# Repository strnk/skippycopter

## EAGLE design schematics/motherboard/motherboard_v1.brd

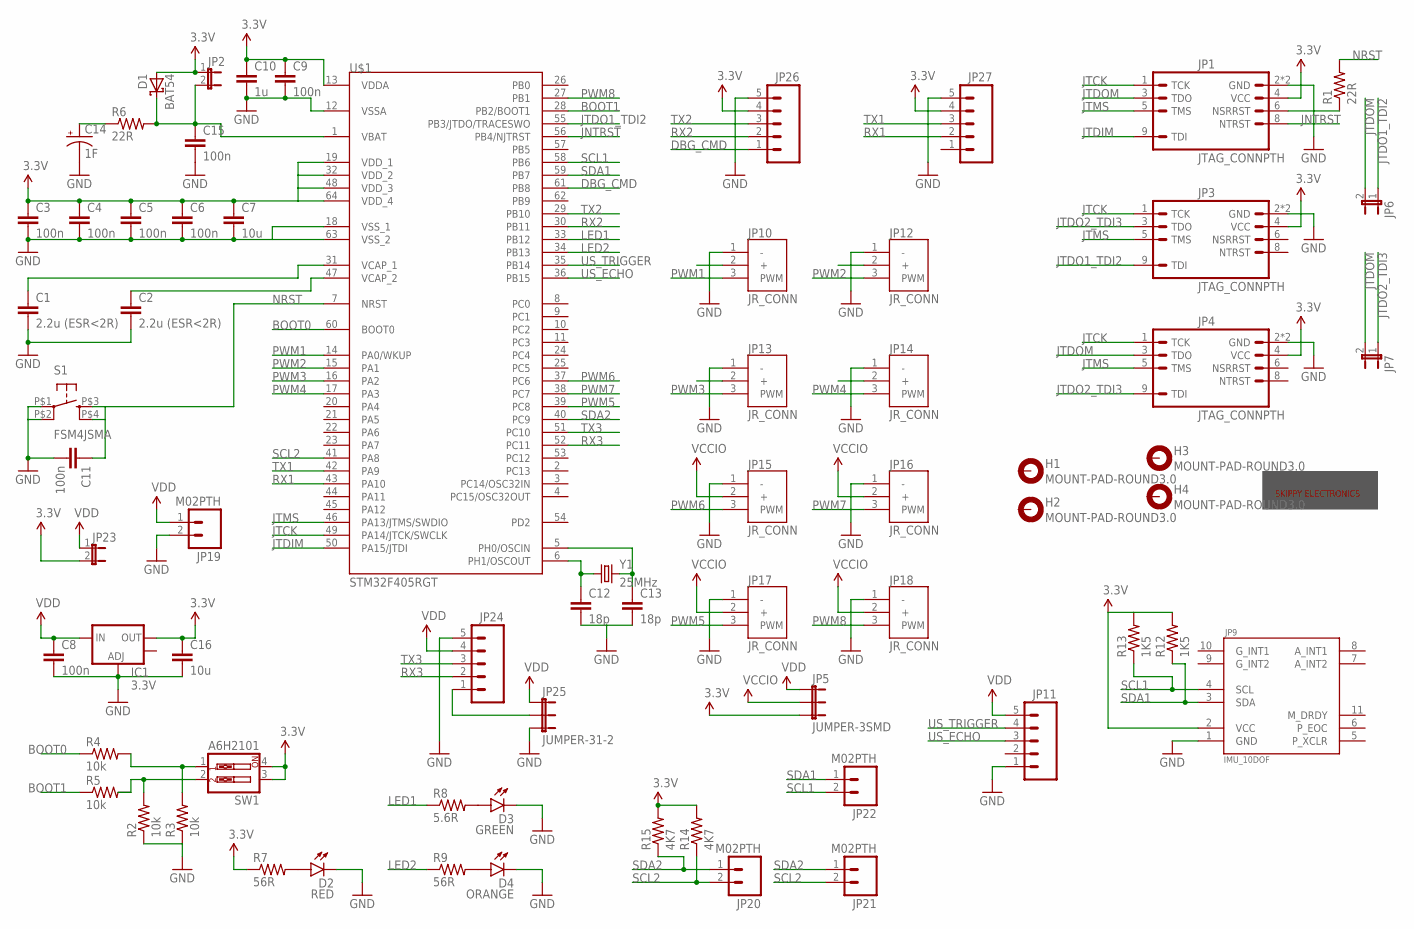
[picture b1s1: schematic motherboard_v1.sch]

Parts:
C1, C2: 2.2u (ESR<2R); 1206
C3, C4, C5, C6, C9, C15: 100n; 0805
C7, C16: 10u; 1206
C8, C11: 100n; 1206
C10: 1u; 1206
C12, C13: 18p; 1206
C14: 1F; CPOL-RADIAL-D165-P508
D1: BAT54; SOT23
D2: RED; LED-1206
D3: GREEN; LED-1206
D4: ORANGE; LED-1206
H1, H2, H3, H4: MOUNT-PAD-ROUND3.0; 3,0-PAD
IC1: 3.3V; SOT223
JP1, JP3, JP4: JTAG_CONNPTH; AVR_ICSP
JP2, JP6, JP7, JP23: JUMPER-2SMD-NO; SJ_2S-NO
JP5: JUMPER-3SMD; SJ_3
JP9: IMU_10DOF
JP10, JP12, JP13, JP14, JP15, JP16, JP17, JP18: JR_CONN; 1X03
JP11, JP24, JP26, JP27: M05PTH; 1X05
JP19, JP20, JP21, JP22: M02PTH; 1X02
JP25: JUMPER-31-2; SJ_3_PASTE1&2
R1, R6: 22R; 1206
R2, R3, R4, R5: 10k; 1206
R7, R9: 56R; 1206
R8: 5.6R; 1206
R12, R13: 1K5; 1206
R14, R15: 4K7; 1206
S1: FSM4JSMA; TYCO-FSM4JSMA
SW1: A6H2101; DIPSWITCH-02-50MIL
U$1: STM32F405RGT; LQFP-ST-64-2
U$2: SKIPPYTXT-PLC-10MM
Y1: 25MHz; HC49UP

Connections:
3.3V: C3.1, C4.1, C5.1, C6.1, C7.1, C9.1, C10.1, C16.1, D1.1 (A), IC1.2 (OUT), JP1.4 (VCC), JP2.1, JP3.4 (VCC), JP4.4 (VCC), JP5.3, JP9.2 (VCC), JP23.2, JP26.4, JP27.4, R7.1, R12.2, R13.2, R14.2, R15.2, SW1.3, SW1.4, U$1.13 (VDDA), U$1.19 (VDD_1), U$1.32 (VDD_2), U$1.48 (VDD_3), U$1.64 (VDD_4)
BOOT0: R4.1, U$1.60 (BOOT0)
BOOT1: R5.1, U$1.28 (PB2/BOOT1)
DBG_CMD: JP26.1, U$1.61 (PB8)
GND: C1.2, C2.2, C3.2, C4.2, C5.2, C6.2, C7.2, C8.2, C9.2, C10.2, C11.2, C12.2, C13.2, C14.2 (-), C15.2, C16.2, D2.C, D3.C, D4.C, IC1.1 (ADJ), JP1.2 (GND), JP1.10 (GND), JP3.2 (GND), JP3.10 (GND), JP4.2 (GND), JP4.10 (GND), JP9.1 (GND), JP10.1 (-), JP11.1, JP12.1 (-), JP13.1 (-), JP14.1 (-), JP15.1 (-), JP16.1 (-), JP17.1 (-), JP18.1 (-), JP19.2, JP24.5, JP25.3, JP26.5, JP27.5, R2.1, R3.1, S1.P$1 (1), S1.P$2 (2), U$1.12 (VSSA), U$1.18 (VSS_1), U$1.63 (VSS_2)
JNTRST: JP1.8 (NTRST), U$1.56 (PB4/NJTRST)
JTCK: JP1.1 (TCK), JP3.1 (TCK), JP4.1 (TCK), U$1.49 (PA14/JTCK/SWCLK)
JTDIM: JP1.9 (TDI), U$1.50 (PA15/JTDI)
JTDO1_TDI2: JP3.9 (TDI), JP6.1, U$1.55 (PB3/JTDO/TRACESWO)
JTDO2_TDI3: JP3.3 (TDO), JP4.9 (TDI), JP7.1
JTDOM: JP1.3 (TDO), JP4.3 (TDO), JP6.2, JP7.2
JTMS: JP1.5 (TMS), JP3.5 (TMS), JP4.5 (TMS), U$1.46 (PA13/JTMS/SWDIO)
LED1: R8.1, U$1.33 (PB12)
LED2: R9.1, U$1.34 (PB13)
unnamed: C1.1, U$1.31 (VCAP_1)
unnamed: C2.1, U$1.47 (VCAP_2)
unnamed: C12.1, U$1.6 (PH1/OSCOUT), Y1.1
unnamed: JP1.6 (NSRRST), R1.1
unnamed: C13.1, U$1.5 (PH0/OSCIN), Y1.2
unnamed: R3.2, R4.2, SW1.1
unnamed: R2.2, R5.2, SW1.2
unnamed: D2.A, R7.2
unnamed: C14.1 (+), R6.1
unnamed: C15.1, D1.3 (C), JP2.2, R6.2, U$1.1 (VBAT)
unnamed: D3.A, R8.2
unnamed: JP24.1, JP25.2
unnamed: D4.A, R9.2
NRST: C11.1, R1.2, S1.P$3 (3), S1.P$4 (4), U$1.7 (NRST)
PWM1: JP10.3 (PWM), U$1.14 (PA0/WKUP)
PWM2: JP12.3 (PWM), U$1.15 (PA1)
PWM3: JP13.3 (PWM), U$1.16 (PA2)
PWM4: JP14.3 (PWM), U$1.17 (PA3)
PWM5: JP17.3 (PWM), U$1.39 (PC8)
PWM6: JP15.3 (PWM), U$1.37 (PC6)
PWM7: JP16.3 (PWM), U$1.38 (PC7)
PWM8: JP18.3 (PWM), U$1.27 (PB1)
RX1: JP27.2, U$1.43 (PA10)
RX2: JP26.2, U$1.30 (PB11)
RX3: JP24.2, U$1.52 (PC11)
SCL1: JP9.4 (SCL), JP22.2, R13.1, U$1.58 (PB6)
SCL2: JP20.2, JP21.2, R14.1, U$1.41 (PA8)
SDA1: JP9.3 (SDA), JP22.1, R12.1, U$1.59 (PB7)
SDA2: JP20.1, JP21.1, R15.1, U$1.40 (PC9)
TX1: JP27.3, U$1.42 (PA9)
TX2: JP26.3, U$1.29 (PB10)
TX3: JP24.3, U$1.51 (PC10)
US_ECHO: JP11.3, U$1.36 (PB15)
US_TRIGGER: JP11.4, U$1.35 (PB14)
VCCIO: JP5.2, JP15.2 (+), JP16.2 (+), JP17.2 (+), JP18.2 (+)
VDD: C8.1, IC1.3 (IN), JP5.1, JP11.5, JP19.1, JP23.1, JP24.4, JP25.1

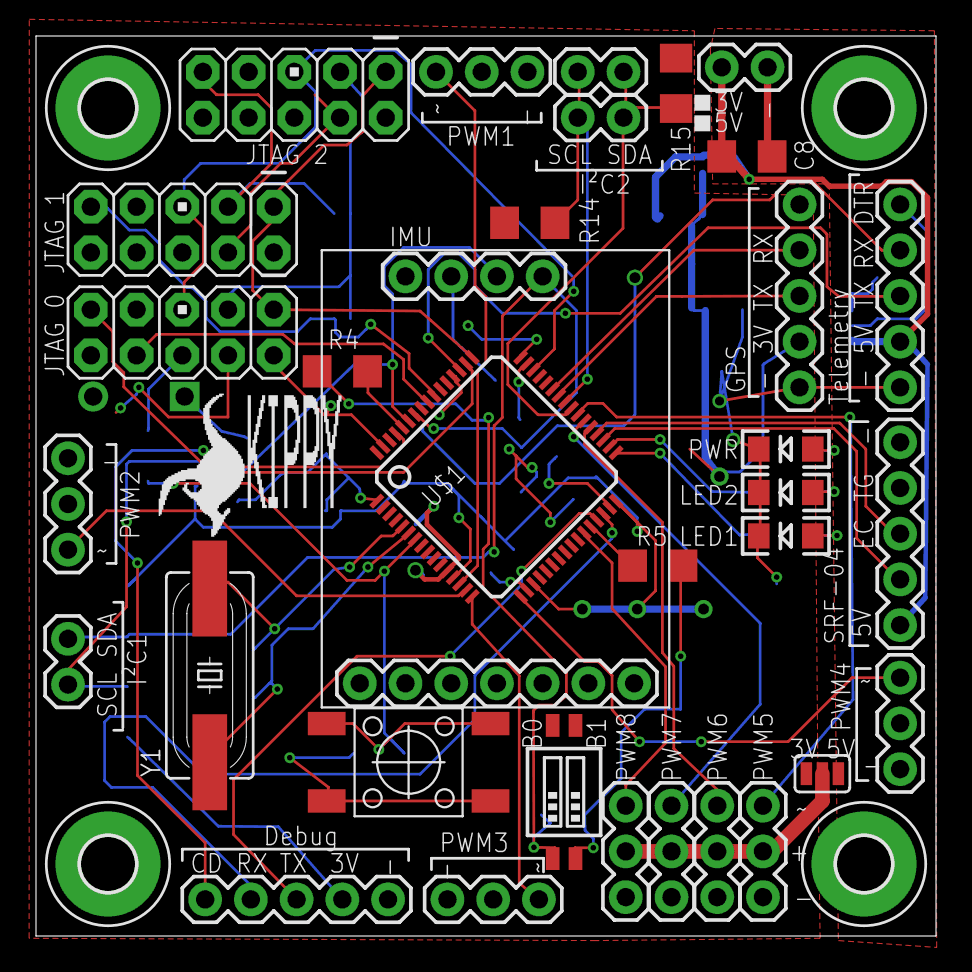
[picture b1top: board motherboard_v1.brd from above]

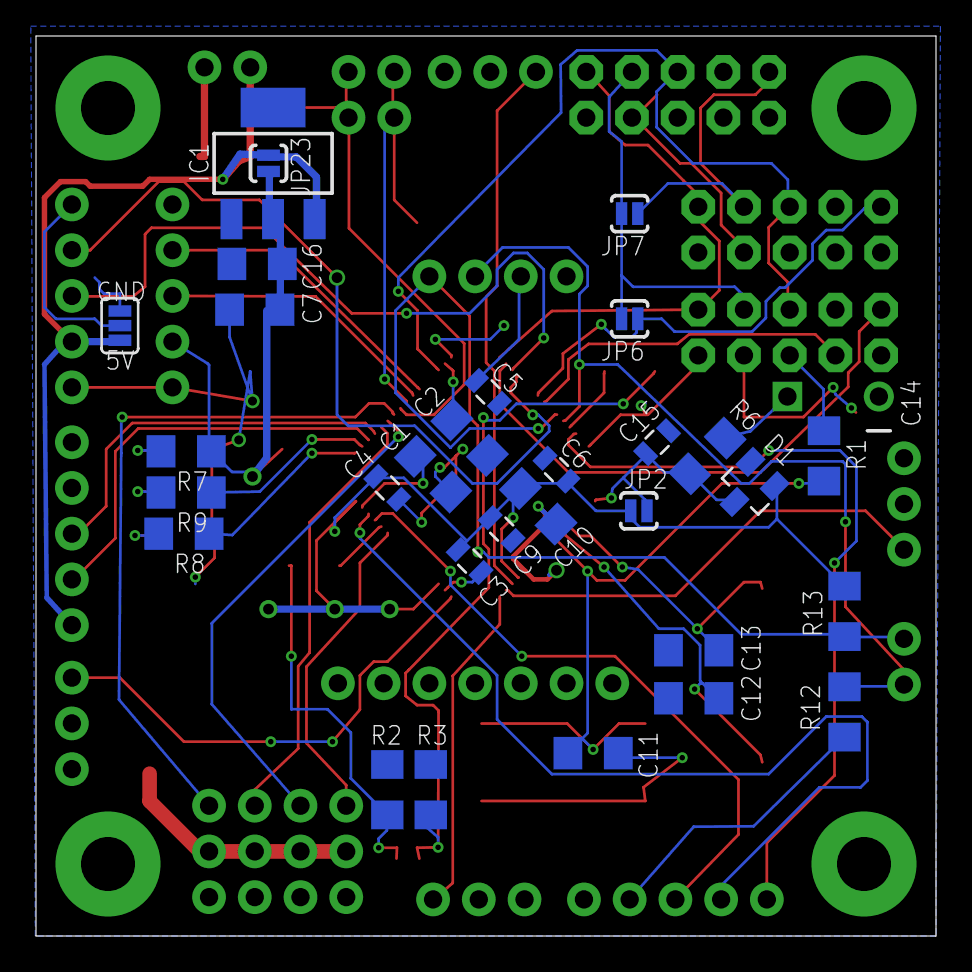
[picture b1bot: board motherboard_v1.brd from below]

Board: 2 copper layers, 50.0 x 50.0 mm, 69 parts (31 on the bottom side), 50 nets.

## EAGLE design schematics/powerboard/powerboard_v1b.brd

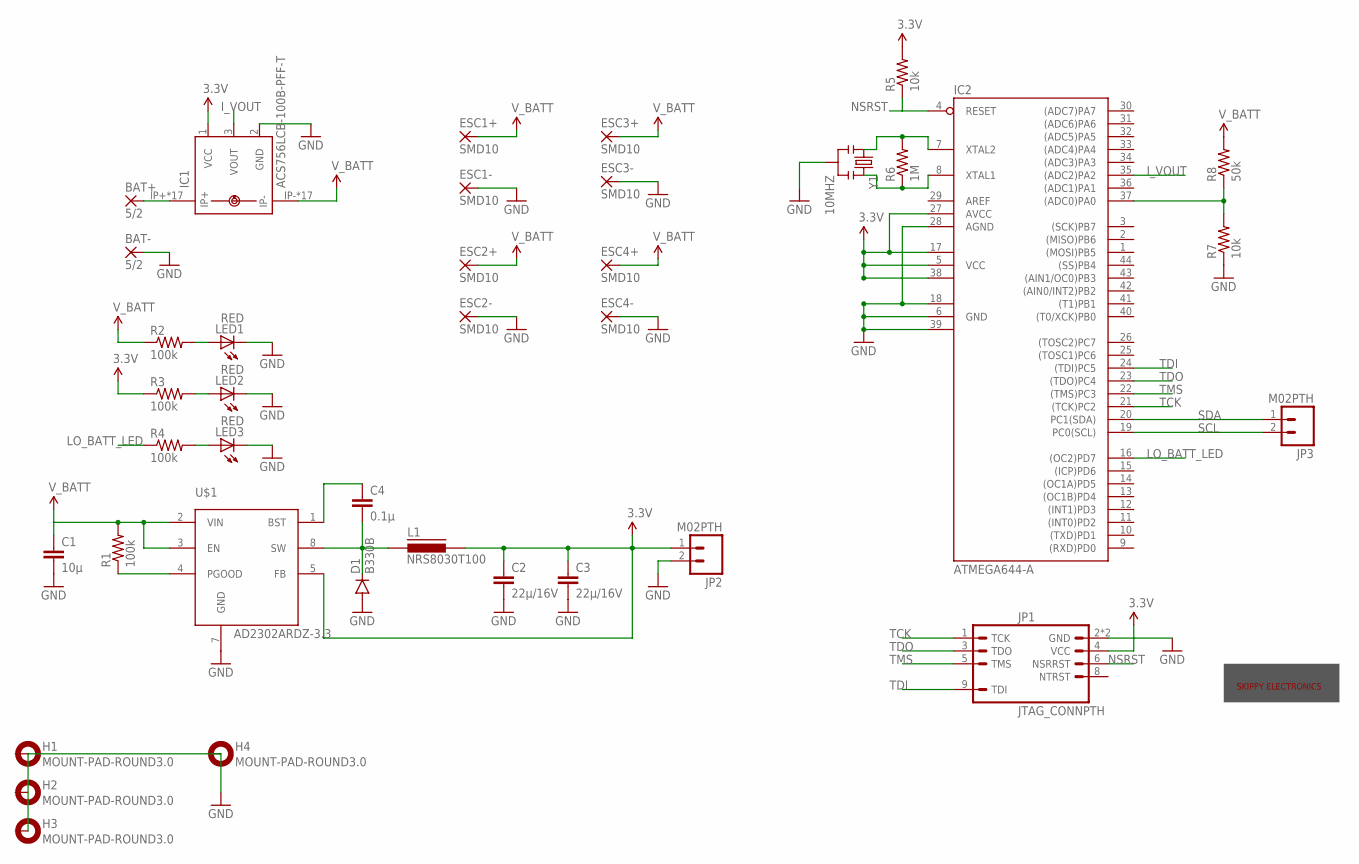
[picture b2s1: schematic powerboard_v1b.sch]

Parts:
BAT+: 5/2
BAT-: 5/2
C1: 10µ; 1206
C2, C3: 22µ/16V; 1206
C4: 0.1µ; 1206
D1: B330B; SMB-DIODE
ESC1+, ESC1-, ESC2+, ESC2-, ESC3+, ESC3-, ESC4+, ESC4-: SMD10; SMD5.08-10.16
H1, H2, H3, H4: MOUNT-PAD-ROUND3.0; 3,0-PAD
IC1: ACS756LCB-100B-PFF-T; CB-PFF
IC2: ATMEGA644-A; TQFP44
JP1: JTAG_CONNPTH; AVR_ICSP
JP2, JP3: M02PTH; 1X02
L1: NRS8030T100; NRS8030
LED1, LED2, LED3: RED; LED_1206
R1, R2, R3, R4: 100k; 1206
R5, R7: 10k; 1206
R6: 1M; 1206
R8: 50k; 1206
U$1: AD2302ARDZ-3.3; SO8
U$2: SKIPPYTXT-PLC-10MM
Y1: 10MHZ; RESONATOR-SMD

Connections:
3.3V: C2.1, C3.1, IC1.1 (VCC), IC2.5 (VCC), IC2.17 (VCC1), IC2.27 (AVCC), IC2.38 (VCC2), JP1.4 (VCC), JP2.1, L1.P$2 (2), R3.1, R5.2, U$1.5 (FB)
GND: BAT-.P$1, C1.2, C2.2, C3.2, D1.A, ESC1-.P$1, ESC1-.P$2, ESC2-.P$1, ESC2-.P$2, ESC3-.P$1, ESC3-.P$2, ESC4-.P$1, ESC4-.P$2, IC1.2 (GND), IC2.6 (GND), IC2.18 (GND1), IC2.28 (AGND), IC2.39 (GND2), JP1.2 (GND), JP1.10 (GND), JP2.2, LED1.C, LED2.C, LED3.C, R7.1, U$1.7 (GND), Y1.2
I_VOUT: IC1.3 (VOUT), IC2.35 ((ADC2)PA2)
LO_BATT_LED: IC2.16 ((OC2)PD7), R4.1
unnamed: BAT+.P$1, IC1.IP+, IC1.IP+@2 (IP+), IC1.IP+@3 (IP+), IC1.IP+@4 (IP+), IC1.IP+@5 (IP+), IC1.IP+@6 (IP+), IC1.IP+@7 (IP+), IC1.IP+@8 (IP+), IC1.IP+@9 (IP+), IC1.IP+@10 (IP+), IC1.IP+@11 (IP+), IC1.IP+@12 (IP+), IC1.IP+@13 (IP+), IC1.IP+@14 (IP+), IC1.IP+@15 (IP+), IC1.IP+@16 (IP+), IC1.IP+@17 (IP+)
unnamed: C4.2, D1.C, L1.P$1 (1), U$1.8 (SW)
unnamed: R1.1, U$1.4 (PGOOD)
unnamed: LED1.A, R2.2
unnamed: C4.1, U$1.1 (BST)
unnamed: LED2.A, R3.2
unnamed: LED3.A, R4.2
unnamed: IC2.7 (XTAL2), R6.2, Y1.1
unnamed: IC2.8 (XTAL1), R6.1, Y1.3
unnamed: IC2.37 ((ADC0)PA0), R7.2, R8.1
NSRST: IC2.4 (RESET), JP1.6 (NSRRST), R5.1
SCL: IC2.19 (PC0(SCL)), JP3.2
SDA: IC2.20 (PC1(SDA)), JP3.1
TCK: IC2.21 ((TCK)PC2), JP1.1 (TCK)
TDI: IC2.24 ((TDI)PC5), JP1.9 (TDI)
TDO: IC2.23 ((TDO)PC4), JP1.3 (TDO)
TMS: IC2.22 ((TMS)PC3), JP1.5 (TMS)
V_BATT: C1.1, ESC1+.P$1, ESC1+.P$2, ESC2+.P$1, ESC2+.P$2, ESC3+.P$1, ESC3+.P$2, ESC4+.P$1, ESC4+.P$2, IC1.IP-, IC1.IP-@2 (IP-), IC1.IP-@3 (IP-), IC1.IP-@4 (IP-), IC1.IP-@5 (IP-), IC1.IP-@6 (IP-), IC1.IP-@7 (IP-), IC1.IP-@8 (IP-), IC1.IP-@9 (IP-), IC1.IP-@10 (IP-), IC1.IP-@11 (IP-), IC1.IP-@12 (IP-), IC1.IP-@13 (IP-), IC1.IP-@14 (IP-), IC1.IP-@15 (IP-), IC1.IP-@16 (IP-), IC1.IP-@17 (IP-), R1.2, R2.1, R8.2, U$1.2 (VIN), U$1.3 (EN)

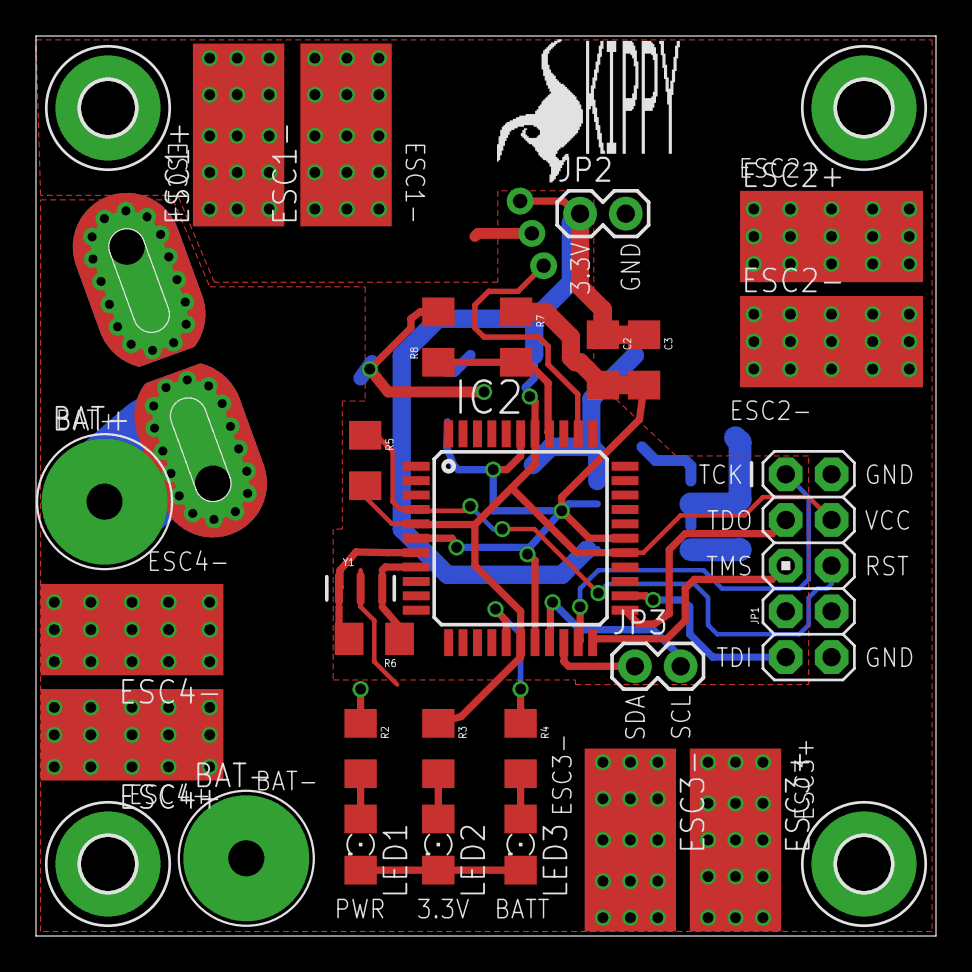
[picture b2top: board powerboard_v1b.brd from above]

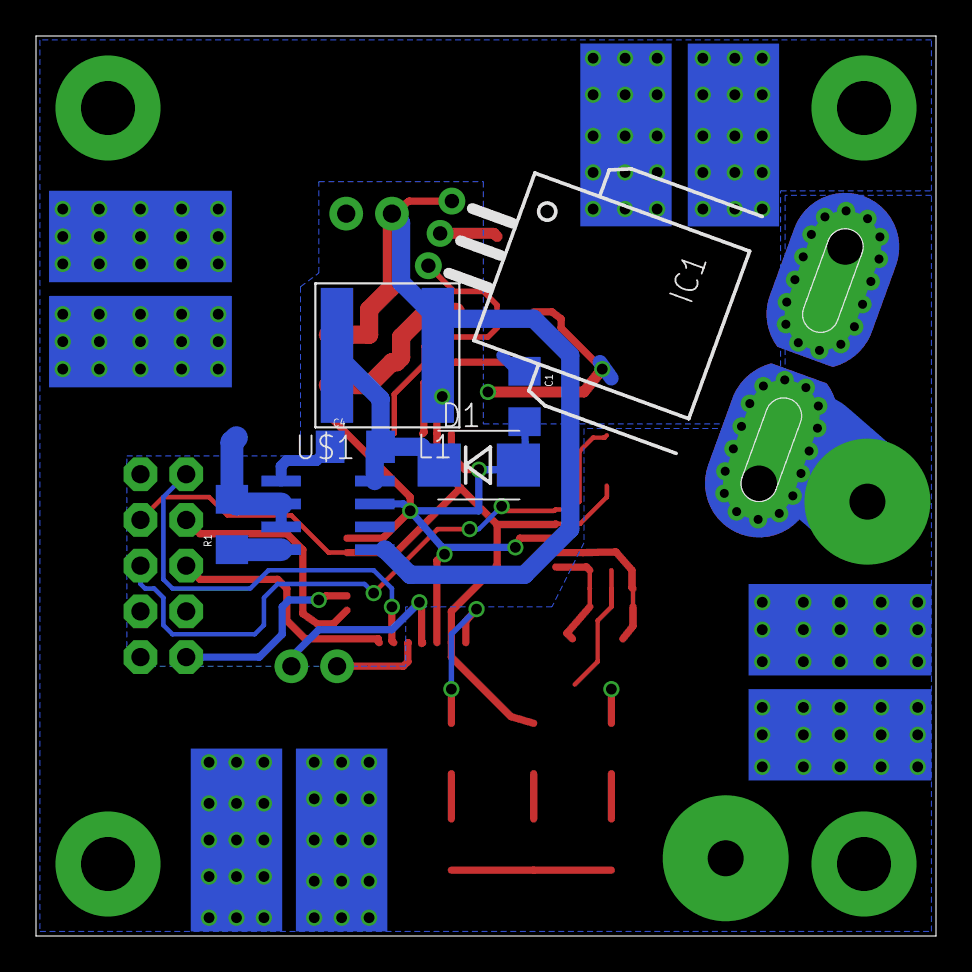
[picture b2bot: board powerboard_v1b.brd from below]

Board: 2 copper layers, 50.0 x 50.0 mm, 39 parts (7 on the bottom side), 22 nets.

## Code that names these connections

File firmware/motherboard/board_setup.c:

#include <libopencm3/stm32/rcc.h>
#include <libopencm3/stm32/gpio.h>
#include "board_setup.h"
#include "config.h"

/* Set STM32 to 168 MHz. */
void clock_setup(void)
{
    rcc_clock_setup_hse_3v3(&hse_25mhz_3v3[CLOCK_3V3_168MHZ]);
}

void gpio_setup(void)
{
    // Enable GPIO clocks
    rcc_periph_clock_enable(RCC_GPIOA);
    rcc_periph_clock_enable(RCC_GPIOB);
    rcc_periph_clock_enable(RCC_GPIOC);
			 
    /* PA0/1/2/3 as TIM2 CH1/2/3/4 */
    gpio_mode_setup(GPIOA, GPIO_MODE_AF, GPIO_PUPD_NONE, GPIO0 | GPIO1 | GPIO2 | GPIO3);
    gpio_set_output_options(GPIOA, GPIO_OTYPE_PP, GPIO_OSPEED_50MHZ, GPIO0 | GPIO1 | GPIO2 | GPIO3);
    gpio_set_af(GPIOA, GPIO_AF1, GPIO0 | GPIO1 | GPIO2 | GPIO3);

    /* PA8 as I2C3 SCL */
    gpio_mode_setup(GPIOA, GPIO_MODE_AF, GPIO_PUPD_NONE, GPIO8);
    gpio_set_output_options(GPIOA, GPIO_OTYPE_OD, GPIO_OSPEED_50MHZ, GPIO8);
    gpio_set_af(GPIOA, GPIO_AF4, GPIO8);

    /* PA9/10 as USART1 TX/RX */
    gpio_mode_setup(GPIOA, GPIO_MODE_AF, GPIO_PUPD_NONE, GPIO9 | GPIO10);
    gpio_set_af(GPIOA, GPIO_AF7, GPIO9 | GPIO10);

    /* PB1 as TIM3 CH4 */
    gpio_mode_setup(GPIOB, GPIO_MODE_AF, GPIO_PUPD_NONE, GPIO1);
    gpio_set_af(GPIOB, GPIO_AF2, GPIO1);

    /* PB6/7 as I2C1 SCL/SDA */
    gpio_mode_setup(GPIOB, GPIO_MODE_AF, GPIO_PUPD_NONE, GPIO6 | GPIO7);
    gpio_set_output_options(GPIOB, GPIO_OTYPE_OD, GPIO_OSPEED_50MHZ, GPIO6 | GPIO7);
    gpio_set_af(GPIOB, GPIO_AF4, GPIO6 | GPIO7);

	/* PB10/11 as USART3 TX/RX */
	gpio_mode_setup(GPIOB, GPIO_MODE_AF, GPIO_PUPD_NONE, GPIO10 | GPIO11);
	gpio_set_af(GPIOB, GPIO_AF7, GPIO10 | GPIO11);

    /* PB12/13 as LED1/LED2 */
    gpio_mode_setup(GPIOB, GPIO_MODE_OUTPUT, GPIO_PUPD_NONE, GPIO12 | GPIO13);

    /* PB14/15 as US_TRIGGER/US_ECHO */
    gpio_mode_setup(GPIOB, GPIO_MODE_OUTPUT, GPIO_PUPD_NONE, GPIO14);
    gpio_mode_setup(GPIOB, GPIO_MODE_INPUT, GPIO_PUPD_NONE, GPIO15);

    /* PC6/7 as TIM3 CH1/2 */
    gpio_mode_setup(GPIOC, GPIO_MODE_AF, GPIO_PUPD_NONE, GPIO6 | GPIO7 | GPIO8);
    gpio_set_af(GPIOC, GPIO_AF2, GPIO6 | GPIO7);

    #ifdef USE_PPM_INPUT
    /* PC8 as TIM8 CH3 */
    gpio_set_af(GPIOC, GPIO_AF3, GPIO8);
    #else
    /* PC8 as TIM3 CH3 */
    gpio_set_af(GPIOC, GPIO_AF2, GPIO8);
    #endif

    /* PC9 as I2C3 SDA */
    gpio_mode_setup(GPIOC, GPIO_MODE_AF, GPIO_PUPD_NONE, GPIO9);
    gpio_set_output_options(GPIOC, GPIO_OTYPE_OD, GPIO_OSPEED_50MHZ, GPIO9);
    gpio_set_af(GPIOC, GPIO_AF4, GPIO9);

    /* PC10/11 as UART4 TX/RX */
    gpio_mode_setup(GPIOC, GPIO_MODE_AF, GPIO_PUPD_NONE, GPIO10 | GPIO11);
    gpio_set_af(GPIOC, GPIO_AF8, GPIO10 | GPIO11);

    // Enable timers clocks
    rcc_periph_clock_enable(RCC_PWM_LO_TIMER);
    rcc_periph_clock_enable(RCC_PWM_HI_TIMER);
    rcc_periph_clock_enable(RCC_PPM_TIMER);

    // Enable UARTs clocks
    rcc_periph_clock_enable(RCC_UART_DEBUG);
    rcc_periph_clock_enable(RCC_UART_GPS);
}

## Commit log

2013-12-06 Directory structure
2013-12-06 Battery docs
2013-12-06 ESC docs
2013-12-06 IMU docs
2013-12-06 Motherboard docs
2013-12-06 Miscellaneous docs
2013-12-21 SeeedStudio libraries and motherboard schematic draft
2013-12-21 New STM32F405RGT symbol in stm32 lib
2013-12-24 Quadricopter sizing excel sheet
2014-01-06 Skippy logos
2014-01-06 Bitmap (300dpi) versions of the logos
2014-01-06 Eagle library of Skippy logos
2014-01-07 Adding documentation for dual USB UART/FIFO FT2232
2015-02-06 ACS756 datasheet + eagle libs
2015-02-07 Eagle lib update & logos
2015-02-08 Added Sparkfun Eagle libs
2015-02-08 Moved Sparkfun lib to 3rd-party
2015-02-08 Changed README to markdown format
2015-02-08 Reorganized libs, added DC/DC buck converter and power board
2015-02-08 Inductor lib and powerboard 5V rail
2015-02-09 Power board finalized
2015-02-09 Power board PCB placement
2015-02-11 New PCB for power board
2015-02-19 Lower resolution logo for Gerber export
2015-02-19 Powerboard PCB and schematics revisions a and b
2015-02-19 Low-resolution logo
2015-02-19 Seeedstudio DRU and CAM update
2015-02-19 Powerboard PCB rev 1b RTM Gerber export for Seeedstudio
2015-02-20 Seeedstudio Powerboard RTM rev 1b fix
2015-05-01 Motherboard schematic draft
2015-05-03 Motherboard reference design
2015-05-04 Library refactor and motherboard update
2015-05-04 Bluetooth debug module and external boards lib. Motherboard update
2015-05-05 Motherboard update and PCB draft
2015-05-06 MB PCB update
2015-05-07 Motherboard update with almost-ready routing
2015-05-08 Motherboard v1 RTM
2015-05-10 Dependencies help file
2015-05-10 Powerboard test firmware
2015-05-10 OpenOCD scripts and global Makefile
2015-05-11 Motherboard printouts and boards documentation
2015-05-17 Chain test with STM32 discovery
2015-05-26 Software dependencies and Monitor UI draft
2015-05-26 Rework of the openOCD scripts to support single card flashing and MB UART test with console support
2015-05-27 Directory typo fix
2015-05-28 Fixes issues #1 and #2
2015-05-28 Motherboard IMU test
2015-05-29 Removed old powerboard revs
2015-05-29 Add the RTM dir to vendored folder in gitattributes
2015-05-29 SkippyMonitor GI/CLI application draft
2015-05-30 Build instruction update for Linux
2015-05-30 Attributes update
2015-05-30 IMU compass example
2015-05-31 Motherboard firmware C++ rework
2015-05-31 I2C write fix and ADXL345 test
2015-05-31 Full IMU draft + temporal scheduler
2015-06-03 Skippy Monitor update with IMU plotting support
2015-06-03 Gyro register reading fix and 115200baud UART. IMU debug
2015-06-03 Documentation update
2015-06-08 L3G4200D reading problem fix
2015-06-08 Madgwick2011 fusion algorithm test with live 3D visualization
2015-07-05 PWM peripheral + ESC arm
2015-07-05 Performance counters
2015-07-05 Small fix. in the Sys. Scheduler debug log
2015-07-06 CLI interface draft. CLI PWM support
2015-07-13 I2C stack and voltage/intensity monitor
2015-07-13 Powerboard flash fix
2015-07-13 System bus support + powerboard V/I readings
2015-07-13 CLI flag support (fd/fe) and hardware madgwick implementation at 500Hz
2015-07-14 Raw attitude data over uart (fe/fd raw_attitude)
2015-07-14 Attitude now supported with AT messages from copter instead of raw sensors. Line edit on main window enabled, use ENTER or Send button to send lines over UART
2015-07-16 Monitor support for raw messages from GPS, draft to display it on a map
2015-07-16 Software dependencies documentation update
2015-07-16 Add support for GPS on USART1 and GPS proxy with gps_proxy flag
2015-07-26 Flag system + PPM receiver/decoder
2015-07-29 Added radio PPM decoder + RF test on one motor. Renamed system messages flags
2015-07-29 Added system messages debugger, cell voltage indicator and charge progressbar

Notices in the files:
parts and their libraries:
SparkFun-Capacitors: Licensing: Creative Commons ShareAlike 4.0 International - https://creativecommons.org/licenses/by-sa/4.0
